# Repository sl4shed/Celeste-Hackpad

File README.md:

# Celestepad

A custom keypad made for Celeste with KiCad, OnShape and QMK.

# About

I made this project because I wanted a portable way to play Celeste on my phone with decent controls.
It's just a simple keypad which you can plug into your phone.

# Index
I split this up into multiple readmes for simplicity. Feel free to look around the repo or just use this index:
 - [Assembly Guide](/assembly/README.md)
 - [KiCAD Readme](/kicad/README.md)
 - [QMK Readme](/qmk/readme.md)
 - [CAD Readme](/step/README.md)

# Attribution

I used some of the code in [nwii/oledbongocat](https://github.com/nwii/oledbongocat) for my firmware.

# Finished Build

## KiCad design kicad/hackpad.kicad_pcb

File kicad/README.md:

# KiCAD

This project was made with KiCad 9.
If any 3D models don't show up, check the individual symbols, maybe they should be cached? I'm not that familiar with KiCad so IDK.

# Ordering the PCB
I recommend using the fabrication toolkit plugin to generate the gerber files. You can find it in the KiCad Plugin and Content manager.

As for where to order, I recommend [JLCPCB](https://jlcpcb.com). <br />
This board doesn't require any special settings, just upload the gerber and let it figure it out for you. (For reference, the board dimensions are 185mm*40mm).

# Additional Images
### PCB

### Schematic

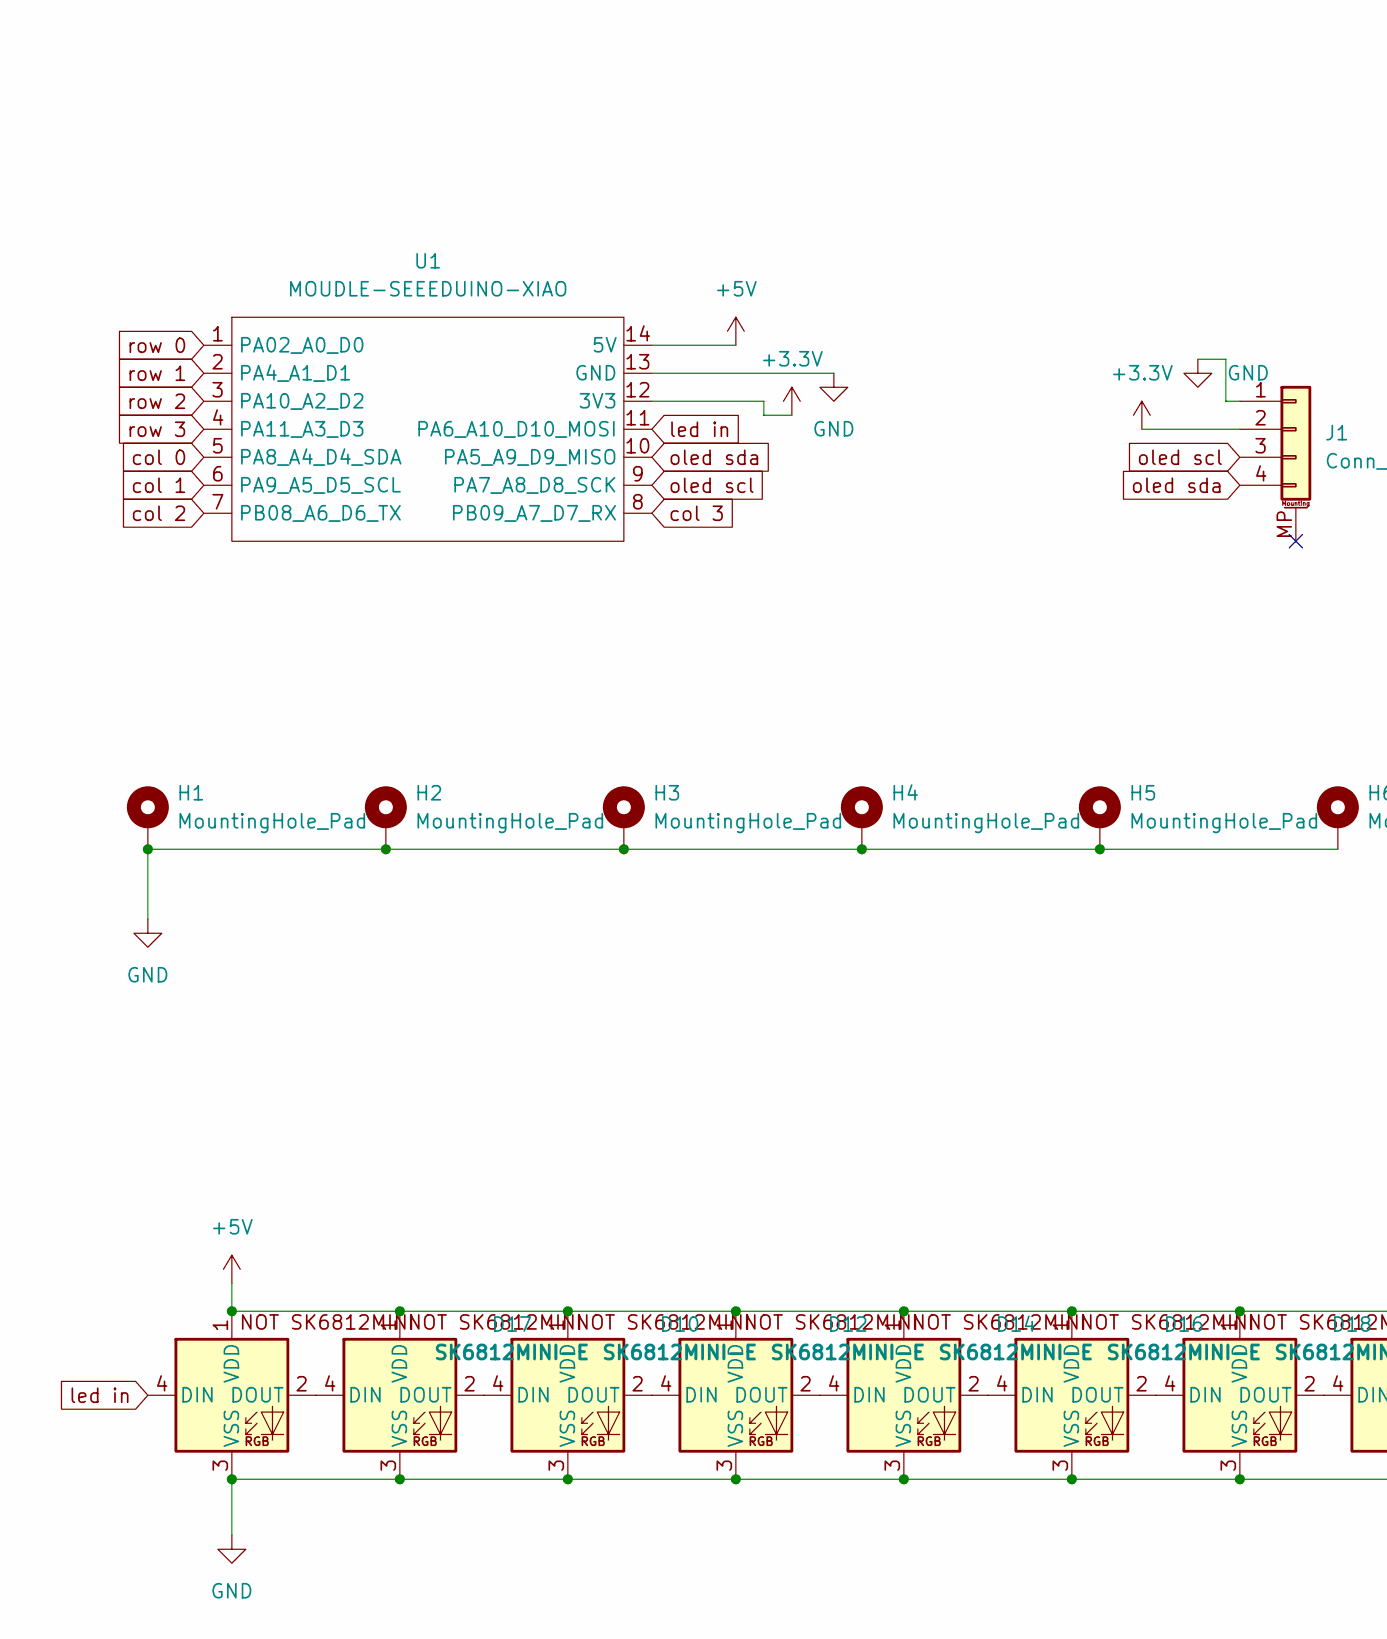
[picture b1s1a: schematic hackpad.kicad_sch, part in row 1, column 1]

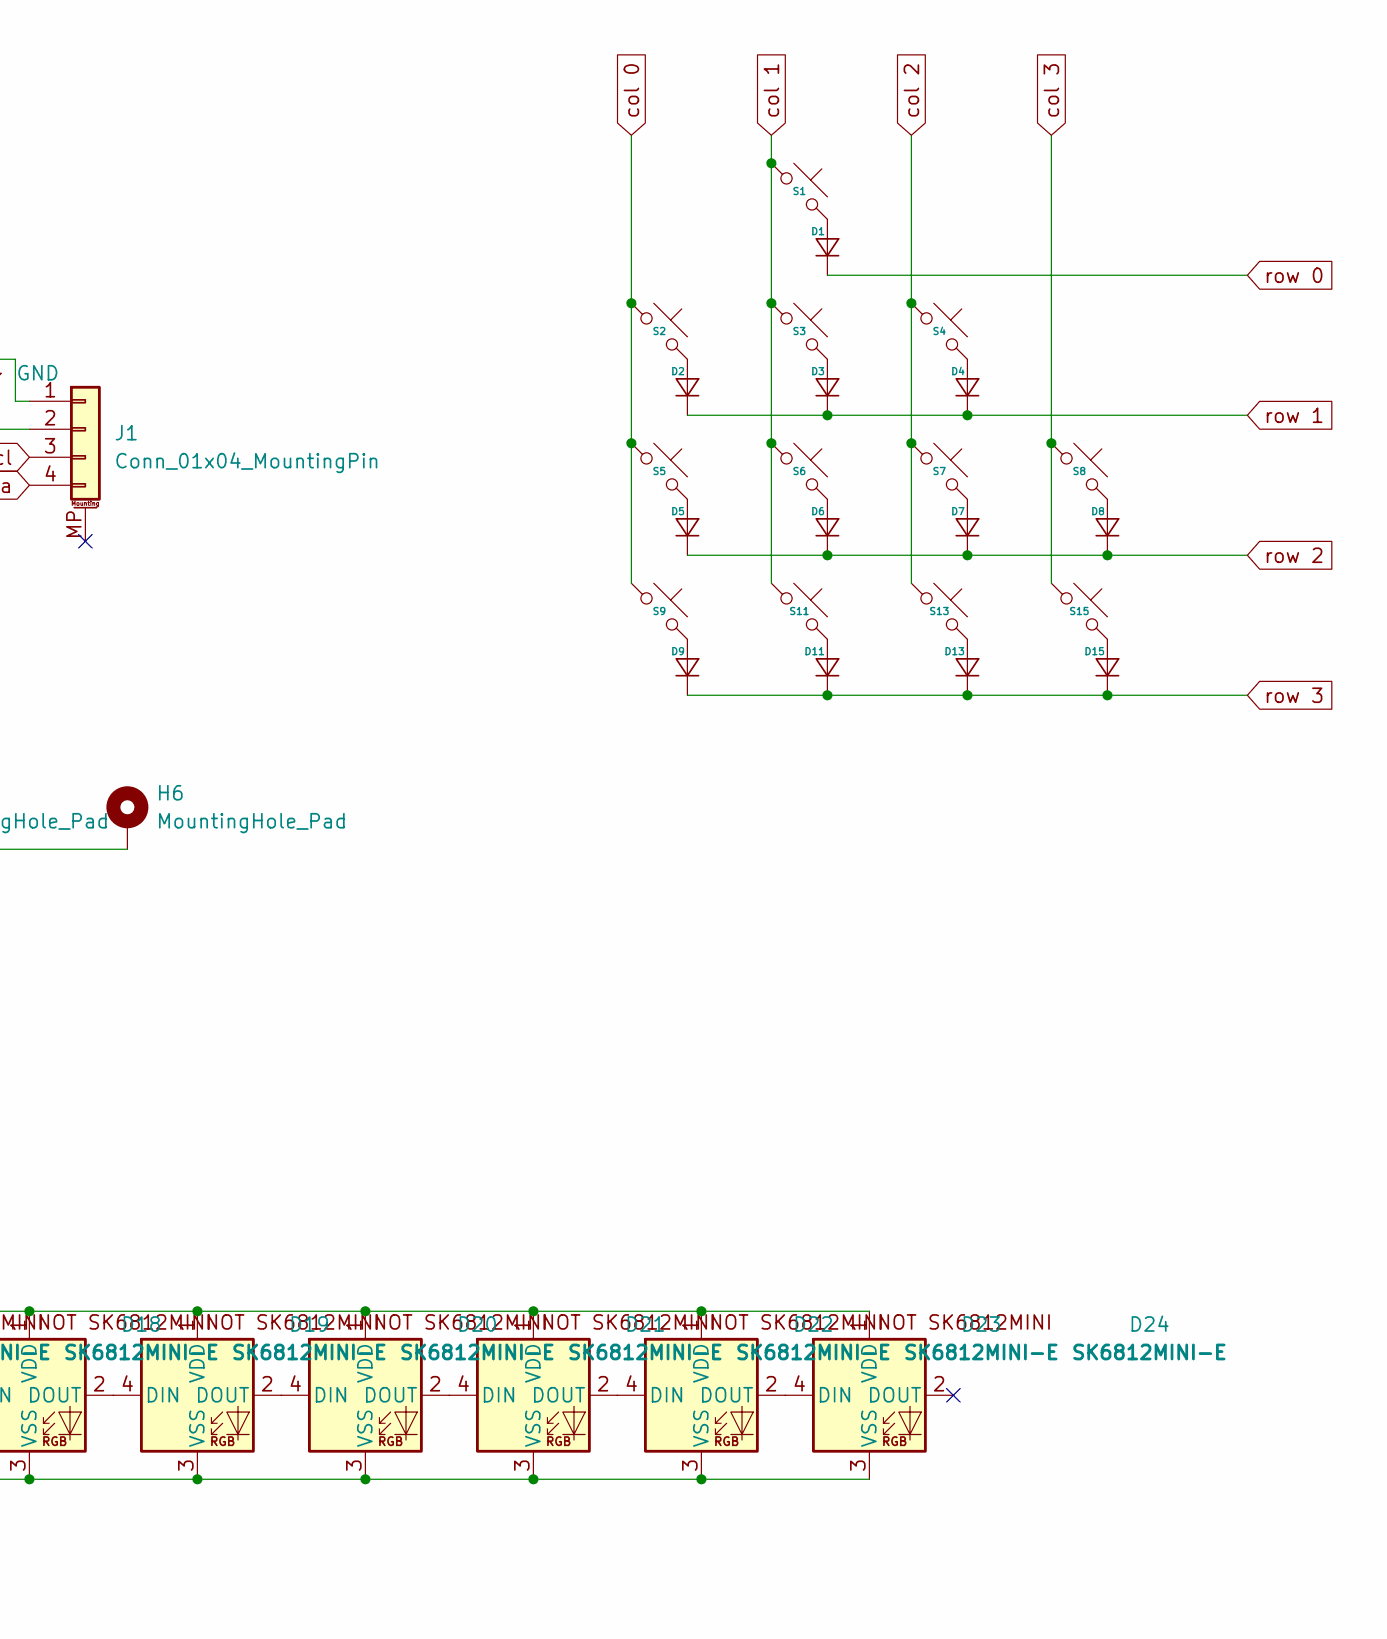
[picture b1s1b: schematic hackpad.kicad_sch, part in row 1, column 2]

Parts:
D1, D2, D3, D4, D5, D6, D7, D8, D9, D11, D13, D15: D_DO-35_SOD27_P7.62mm_Horizontal
D10, D12, D14, D16, D17, D18, D19, D20, D21, D22, D23, D24: SK6812MINI-E; SK6812MINI-E_fixed
H1, H2, H3, H4, H5, H6: MountingHole_Pad; MountingHole_3mm_Pad
J1: Conn_01x04_MountingPin; SSD1306-0.91-OLED-4pin-128x32
S1, S2, S3, S4, S5, S6, S7, S8, S9, S11, S13, S15: SW_Cherry_MX_1.00u_PCB
U1: MOUDLE-SEEEDUINO-XIAO; XIAO-RP2040-DIP

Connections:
+3.3V: J1.2, U1.12 (3V3)
+5V: D10.1 (VDD), D12.1 (VDD), D14.1 (VDD), D16.1 (VDD), D17.1 (VDD), D18.1 (VDD), D19.1 (VDD), D20.1 (VDD), D21.1 (VDD), D22.1 (VDD), D23.1 (VDD), D24.1 (VDD), U1.14 (5V)
GND: D10.3 (VSS), D12.3 (VSS), D14.3 (VSS), D16.3 (VSS), D17.3 (VSS), D18.3 (VSS), D19.3 (VSS), D20.3 (VSS), D21.3 (VSS), D22.3 (VSS), D23.3 (VSS), D24.3 (VSS), H1.1, H2.1, H3.1, H4.1, H5.1, H6.1, J1.1, U1.13 (GND)
unnamed: D1.2 (A), S1.2
unnamed: D2.2 (A), S2.2
unnamed: D3.2 (A), S3.2
unnamed: D4.2 (A), S4.2
unnamed: D5.2 (A), S5.2
unnamed: D6.2 (A), S6.2
unnamed: D7.2 (A), S7.2
unnamed: D8.2 (A), S8.2
unnamed: D9.2 (A), S9.2
unnamed: D10.4 (DIN), D17.2 (DOUT)
unnamed: D10.2 (DOUT), D12.4 (DIN)
unnamed: D11.2 (A), S11.2
unnamed: D12.2 (DOUT), D14.4 (DIN)
unnamed: D13.2 (A), S13.2
unnamed: D14.2 (DOUT), D16.4 (DIN)
unnamed: D15.2 (A), S15.2
unnamed: D16.2 (DOUT), D18.4 (DIN)
unnamed: D18.2 (DOUT), D19.4 (DIN)
unnamed: D19.2 (DOUT), D20.4 (DIN)
unnamed: D20.2 (DOUT), D21.4 (DIN)
unnamed: D21.2 (DOUT), D22.4 (DIN)
unnamed: D22.2 (DOUT), D23.4 (DIN)
unnamed: D23.2 (DOUT), D24.4 (DIN)
col 0: S2.1, S5.1, S9.1, U1.5 (PA8_A4_D4_SDA)
col 1: S1.1, S3.1, S6.1, S11.1, U1.6 (PA9_A5_D5_SCL)
col 2: S4.1, S7.1, S13.1, U1.7 (PB08_A6_D6_TX)
col 3: S8.1, S15.1, U1.8 (PB09_A7_D7_RX)
led in: D17.4 (DIN), U1.11 (PA6_A10_D10_MOSI)
oled scl: J1.3, U1.9 (PA7_A8_D8_SCK)
oled sda: J1.4, U1.10 (PA5_A9_D9_MISO)
row 0: D1.1 (K), U1.1 (PA02_A0_D0)
row 1: D2.1 (K), D3.1 (K), D4.1 (K), U1.2 (PA4_A1_D1)
row 2: D5.1 (K), D6.1 (K), D7.1 (K), D8.1 (K), U1.3 (PA10_A2_D2)
row 3: D9.1 (K), D11.1 (K), D13.1 (K), D15.1 (K), U1.4 (PA11_A3_D3)

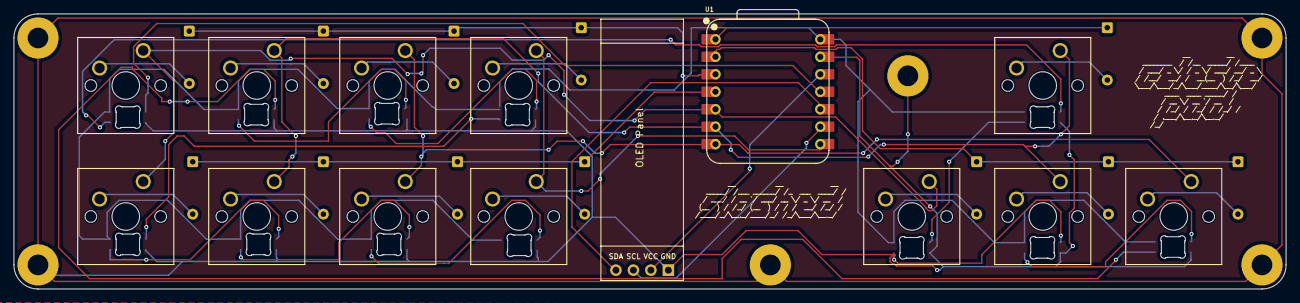
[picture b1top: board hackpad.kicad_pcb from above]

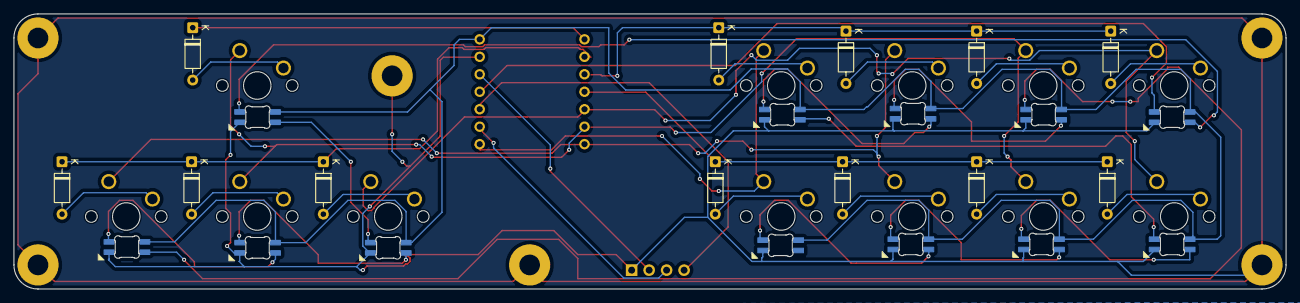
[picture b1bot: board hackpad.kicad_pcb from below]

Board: 2 copper layers, 184.9 x 40.0 mm, 44 parts (12 on the bottom side), 37 nets.

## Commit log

2026-02-07 Upload KiCad PCB files
2026-02-09 update kicad
2026-02-11 pluh
2026-02-12 add assembled keyboard STEP file
2026-02-12 update readmes
2026-02-12 add attribution
2026-02-12 add about
2026-02-12 Update CAD files
2026-02-13 update CAD AGAIN
2026-02-13 weenis
2026-02-17 update pcb to run leds on 5v
2026-04-04 fix qmk firmware
2026-04-04 port to vial
